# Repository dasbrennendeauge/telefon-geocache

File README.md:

# Telefon-Geocache

Ein Geocache, der in einem alten Telefon steckt. Wer den Cache findet, nimmt den
Hörer ab und wird per Sprachansage und Display durch ein kleines Rätsel geführt:
Handynummer eingeben, Münze einwerfen – das Telefon ruft daraufhin **zurück** und
verrät über die angezeigte Rufnummer einen PIN. Wird der PIN korrekt eingegeben,
öffnet ein Relais die Klappe zum Logbuch.

## Spielablauf

Die Firmware ist eine Zustandsmaschine (`step0`–`step7` in `cache/cache.ino`):

| Schritt | Anzeige / Aktion |
|---|---|
| 0 | „Hörer ans Ohr, drücke Taste 5" – GSM-Modul wird initialisiert |
| 1 | Begrüßung; Netz wird gesucht und die Uhrzeit geprüft (nur **8–22 Uhr**, sonst Schritt 7) |
| 2 | Handynummer über das Tastenfeld eingeben, Abschluss mit `#` |
| 3 | „Münze einwerfen" – Wartet auf den Münzeinwurf (Lichtschranke) |
| 4 | Server abfragen (HTTP), Absender-Rufnummer setzen lassen, dann den Spieler **anrufen** (5 s klingeln, NICHT abheben) |
| 5 | Die letzten 4 Ziffern der angezeigten Rufnummer eingeben |
| 6 | Korrekt → Relais öffnet die Klappe; falsch → Hinweis, neuer Versuch |
| 7 | Außerhalb der Öffnungszeiten → Gerät geht in den Tiefschlaf |

Ein 5-Minuten-Countdown läuft global mit; nach Ablauf legt sich das Gerät schlafen.

## So funktioniert der „Rückruf-PIN"

Der eigentliche Trick: Der Spieler muss nicht abnehmen, sondern nur die **angezeigte
Rufnummer** ablesen. Deren letzte 4 Ziffern sind der PIN.

```
Arduino (cache.ino)                        Server (index.php)            sipgate
  │  HTTP GET (über GPRS) ───────────────────▶                              
  │                                          │  PUT /devices/{id}/callerid │
  │                                          │   = +491579999<code>  ──────▶
  │  ◀──────────────── Antwort: <code> ──────┘                              
  │  GPRS trennen                                                           
  │  SIM800L wählt die Handynummer (ATD) ─────────────────────────────────▶ Telefon des
  │  5 s warten, dann auflegen (ATH)                                         Spielers klingelt
  │                                                                          mit +491579999<code>
```

Der Anruf wird seit der Umstellung auf einen **sipgate-neo-PBX-Account** direkt vom
SIM800L aufgebaut (nicht mehr über die sipgate-Click-to-Dial-API – neo erlaubt kein
Nummer-zu-Nummer-Dialing mehr). Der Server setzt nur noch die angezeigte
Absender-Rufnummer und liefert den 4-stelligen Code zurück.

## Projektstruktur

| Pfad | Inhalt |
|---|---|
| `cache/` | Arduino-Firmware (`cache.ino`) + Build-Anleitung (`BUILD.md`) |
| `lib/` | Alle Arduino-Bibliotheken, vendored (siehe unten) |
| `platformio.ini` | PlatformIO-Build-Konfiguration |
| `web-call-starter/` | PHP-Server: setzt Absender-Rufnummer & liefert PIN-Code |
| `mp3/` | Sprachansagen + Skripte zur TTS-Erzeugung (Google Cloud, Azure, AWS Polly) |
| `pcb/` | EAGLE-Schaltplan und Platinen-Layout |
| `experimente/` | Ältere Test-Sketche |

## Hardware

- **Arduino Mega 2560** (Steuerung)
- **SIM800L** GSM-Modul mit sipgate-SIM (Daten + Sprachanruf)
- **DFPlayer Mini** MP3-Modul + Lautsprecher (Sprachansagen)
- **LCD 20×4** mit I²C-Backpack
- **3×4-Tastenfeld** (Matrix)
- **Lichtschranke** als Münzeinwurf-Sensor
- **Relais** SRD-05VDC-SL-C (öffnet die Klappe)
- **Step-Up-Wandler** für die Stromversorgung des SIM800L

### Verdrahtung (Arduino Mega)

| Komponente | Pins |
|---|---|
| Tastenfeld | Zeilen 34, 35, 36, 37 · Spalten 31, 32, 33 |
| Relais | D10 |
| Münzeinwurf (analog) | A13 |
| SIM800L (UART) | `Serial1`: RX1 = D19, TX1 = D18 · 19200 Baud |
| DFPlayer Mini (UART) | `Serial3`: RX3 = D15, TX3 = D14 |
| LCD (I²C) | SDA = D20, SCL = D21 · Adresse `0x27` |

Die GSM-PIN ist in `cache/cache.ino` definiert (`GSM_PIN`).

## Firmware bauen

Der Build läuft reproduzierbar über [PlatformIO](https://platformio.org/) – alle
Details in **[`cache/BUILD.md`](cache/BUILD.md)**. Kurzform (im Repo-Wurzelverzeichnis):

```bash
pio run                 # kompilieren
pio run -t upload       # auf den Arduino Mega 2560 flashen
pio device monitor      # serieller Monitor (115200 Baud)
```

### Bibliotheken (vendored)

Alle Bibliotheken liegen mit fester Version in `lib/`, damit der Build dauerhaft
und ohne Abhängigkeit von der PlatformIO-Registry funktioniert:

| Library | Version | Anmerkung |
|---|---|---|
| TinyGSM | 0.12.0 | GSM/GPRS + Sprachanruf (SIM800) |
| ArduinoHttpClient | 0.6.1 | HTTP-Request an den Server |
| Keypad | 3.1.1 | Tastenfeld |
| DFMiniMp3 | 1.0.5 | bewusst alte Version – ab 1.0.6 inkompatible Callback-API |
| LiquidCrystal_I2C | fdebrabander | LCD-Ansteuerung über I²C |

## Server (`web-call-starter`)

Kleiner PHP-Endpunkt, der bei jedem Aufruf eine zufällige 4-stellige Zahl erzeugt,
diese als Absender-Rufnummer am sipgate-Gerät setzt und den Code als Antwort
zurückgibt.

- **`SIPGATE_CREDENTIALS`** muss als Umgebungsvariable gesetzt sein
  (Base64 von `tokenId:token` des sipgate-Accounts).
- `$deviceId` in `index.php` an das eigene sipgate-Gerät anpassen (neo nutzt oft `e0`/`p0`).
- Keine externen Abhängigkeiten: reines PHP mit cURL, kein Composer nötig.
- `telefoncache.vhost` enthält eine Beispiel-Apache-vHost-Konfiguration.

> Hinweis: Der eigentliche Anruf erfolgt nicht mehr serverseitig, sondern direkt
> vom Arduino (siehe oben).

## Sprachansagen (`mp3`)

Die Ansagen `0001.mp3`–`0008.mp3` entsprechen den Spielschritten und werden vom
DFPlayer Mini abgespielt. Sie lassen sich per Text-to-Speech neu erzeugen; im
Ordner `mp3/` liegen Skripte für **Google Cloud TTS**, **Azure** und **AWS Polly**.
Die zugehörigen Texte stehen in `mp3/texte/`.

## Platine (`pcb`)

EAGLE-Dateien (`*.sch` Schaltplan, `*.brd` Layout) inklusive gerenderter
Vorschaubilder und PDF-Export.

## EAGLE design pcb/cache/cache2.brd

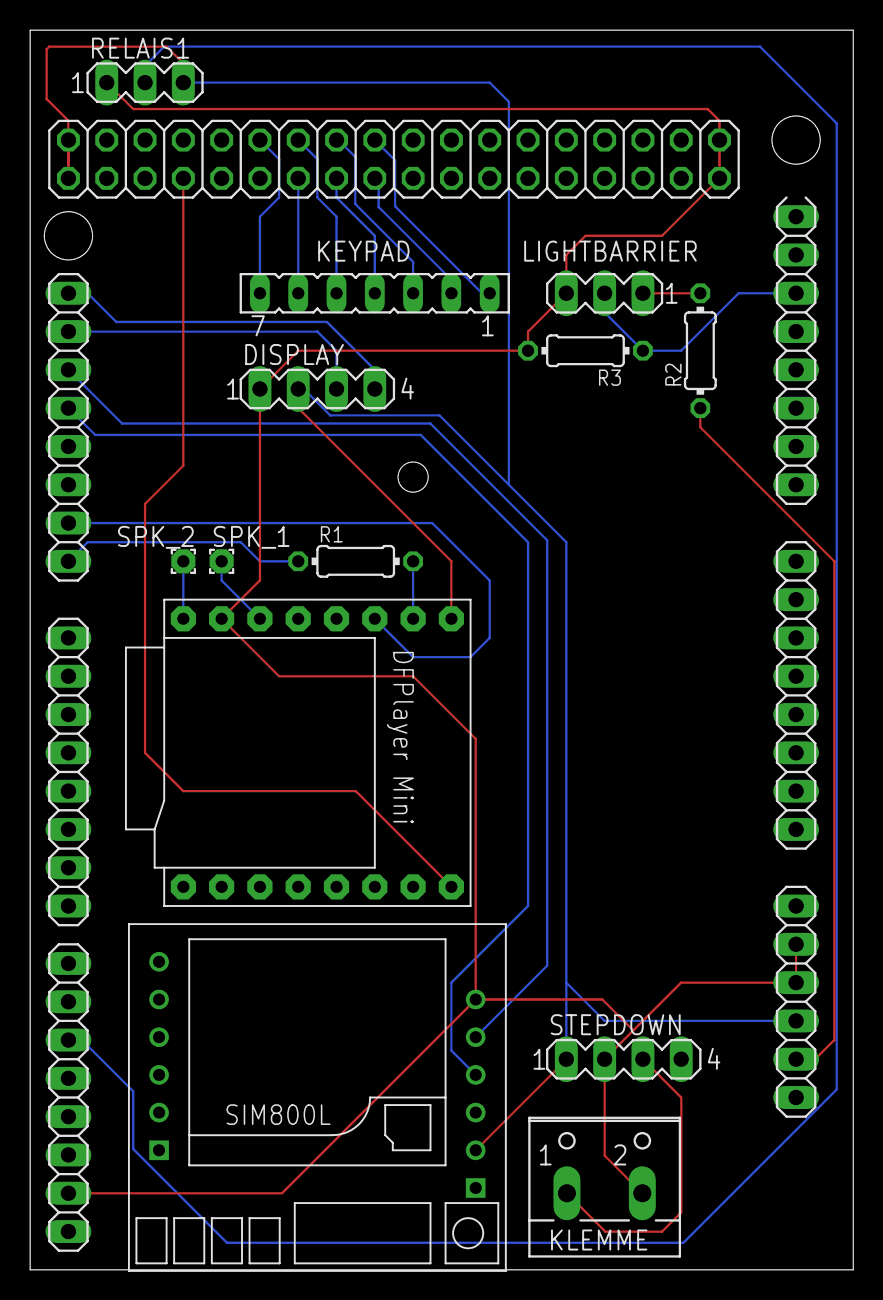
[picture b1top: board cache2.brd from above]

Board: 2 copper layers, 54.6 x 82.2 mm, 14 parts (0 on the bottom side), 24 nets.

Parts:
DISPLAY: MA04-1
IC1: MEGA_ARDUINO
KEYPAD: FE07
KLEMME: W237-102
LIGHTBARRIER: MA03-1
R1, R2, R3: 0204/7
RELAIS1: MA03-1
SPK_1, SPK_2: 1,6/0,8
STEPDOWN: MA04-1
U$1: DFPLAYER
U$2: SIM800LMODULE

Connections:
3V3: LIGHTBARRIER.1, R2.2
+5V: DISPLAY.2, IC1.3, IC1.47, IC1.48, RELAIS1.3, STEPDOWN.1, U$1.VCC, U$2.VCC
GND: DISPLAY.1, IC1.4, IC1.5, IC1.45, IC1.81, IC1.82, KLEMME.2, LIGHTBARRIER.3, R3.2, RELAIS1.1, STEPDOWN.2, U$1.GND_1, U$2.GND
IN+: KLEMME.1, STEPDOWN.3
IN-B: IC1.20, LIGHTBARRIER.2, R3.1
unnamed: IC1.25, U$2.TX
unnamed: IC1.26, U$2.RX
unnamed: IC1.41, RELAIS1.2
unnamed: DISPLAY.3, IC1.24
unnamed: DISPLAY.4, IC1.23
unnamed: IC1.58, KEYPAD.7
unnamed: IC1.59, KEYPAD.6
unnamed: IC1.60, KEYPAD.5
unnamed: IC1.61, KEYPAD.4
unnamed: IC1.62, KEYPAD.3
unnamed: IC1.63, KEYPAD.2
unnamed: IC1.64, KEYPAD.1
unnamed: IC1.30, R1.1
unnamed: IC1.29, U$1.TX
unnamed: R1.2, U$1.RX
unnamed: IC1.2, R2.1
unnamed: SPK_2.1, U$1.SPK2
unnamed: SPK_1.1, U$1.SPK1
unnamed: IC1.53, U$1.BUSY

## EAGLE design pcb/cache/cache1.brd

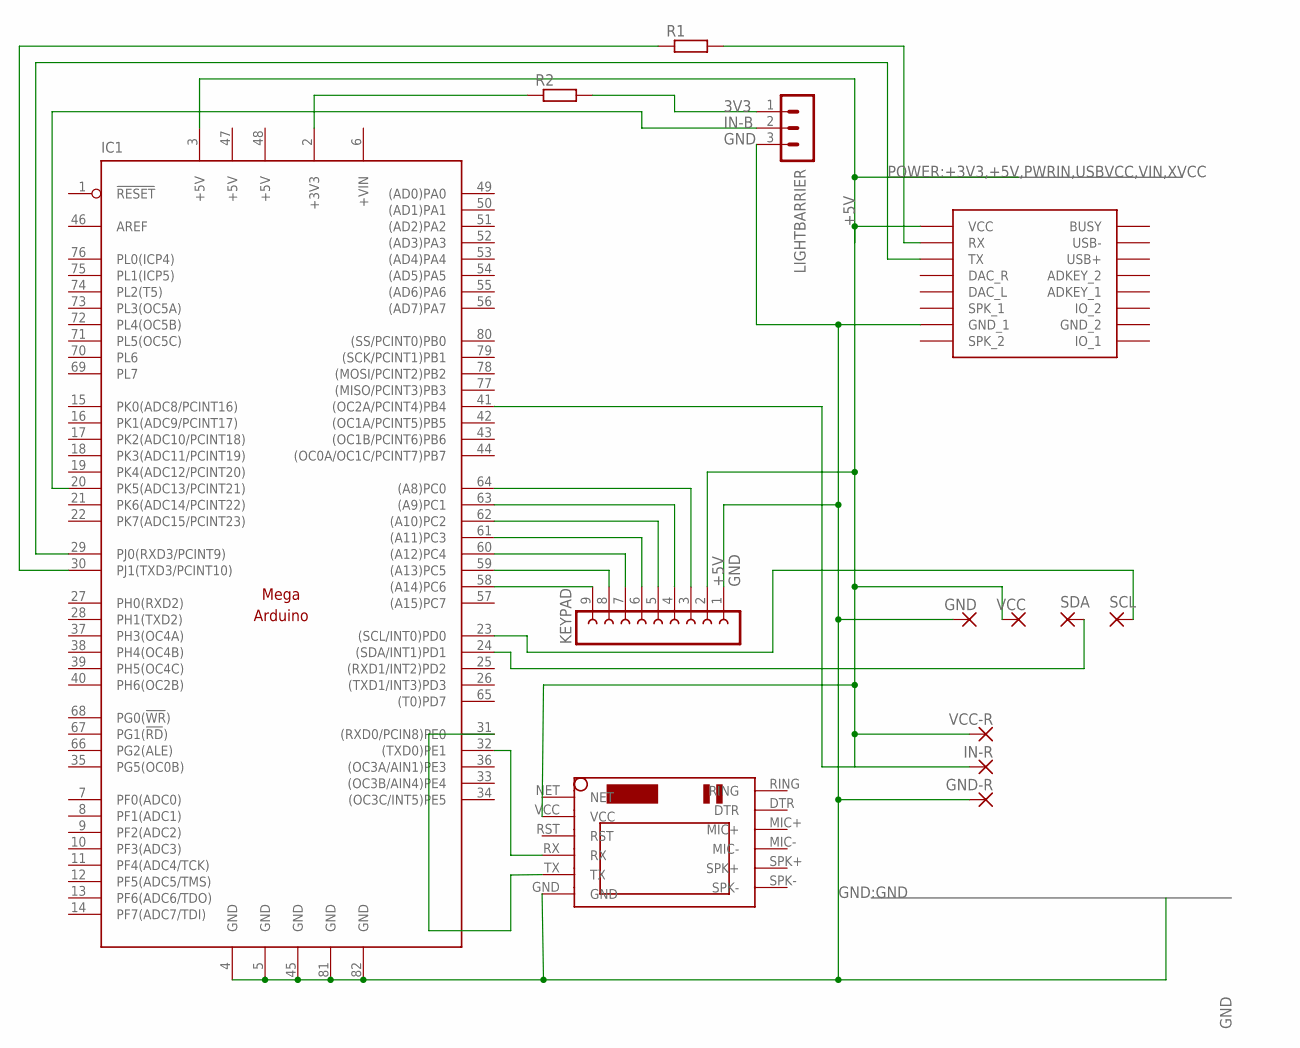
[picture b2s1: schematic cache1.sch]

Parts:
GND: 1,6/0,8
GND-R: 1,6/0,8
IC1: MEGAARDUINO_1; MEGA_ARDUINO
IN-R: 1,6/0,8
KEYPAD: FE09-1; FE09
LIGHTBARRIER: MA03-1
R1, R2: R-EU_0204/7; 0204/7
SCL: 1,6/0,8
SDA: 1,6/0,8
U$1: DFPLAYER
U$2: SIM800LMODULE
VCC: 1,6/0,8
VCC-R: 1,6/0,8

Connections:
3V3: LIGHTBARRIER.1, R2.2
+5V: IC1.3 (+5V), IC1.47 (+5V), IC1.48 (+5V), KEYPAD.2, U$1.VCC, U$2.VCC, VCC.1, VCC-R.1
+VIN: IC1.6 (+VIN)
GND: GND.1, GND-R.1, IC1.4 (GND), IC1.5 (GND), IC1.45 (GND), IC1.81 (GND), IC1.82 (GND), KEYPAD.1, LIGHTBARRIER.3, U$1.GND_1, U$2.GND
IN-B: IC1.20 (PK5(ADC13/PCINT21)), LIGHTBARRIER.2
unnamed: IC1.31 ((RXD0/PCIN8)PE0), U$2.TX
unnamed: IC1.32 ((TXD0)PE1), U$2.RX
unnamed: IC1.41 ((OC2A/PCINT4)PB4), IN-R.1
unnamed: IC1.24 ((SDA/INT1)PD1), SDA.1
unnamed: IC1.23 ((SCL/INT0)PD0), SCL.1
unnamed: IC1.58 ((A14)PC6), KEYPAD.9
unnamed: IC1.59 ((A13)PC5), KEYPAD.8
unnamed: IC1.60 ((A12)PC4), KEYPAD.7
unnamed: IC1.61 ((A11)PC3), KEYPAD.6
unnamed: IC1.62 ((A10)PC2), KEYPAD.5
unnamed: IC1.63 ((A9)PC1), KEYPAD.4
unnamed: IC1.64 ((A8)PC0), KEYPAD.3
unnamed: IC1.30 (PJ1(TXD3/PCINT10)), R1.1
unnamed: IC1.29 (PJ0(RXD3/PCINT9)), U$1.TX
unnamed: R1.2, U$1.RX
unnamed: IC1.2 (+3V3), R2.1

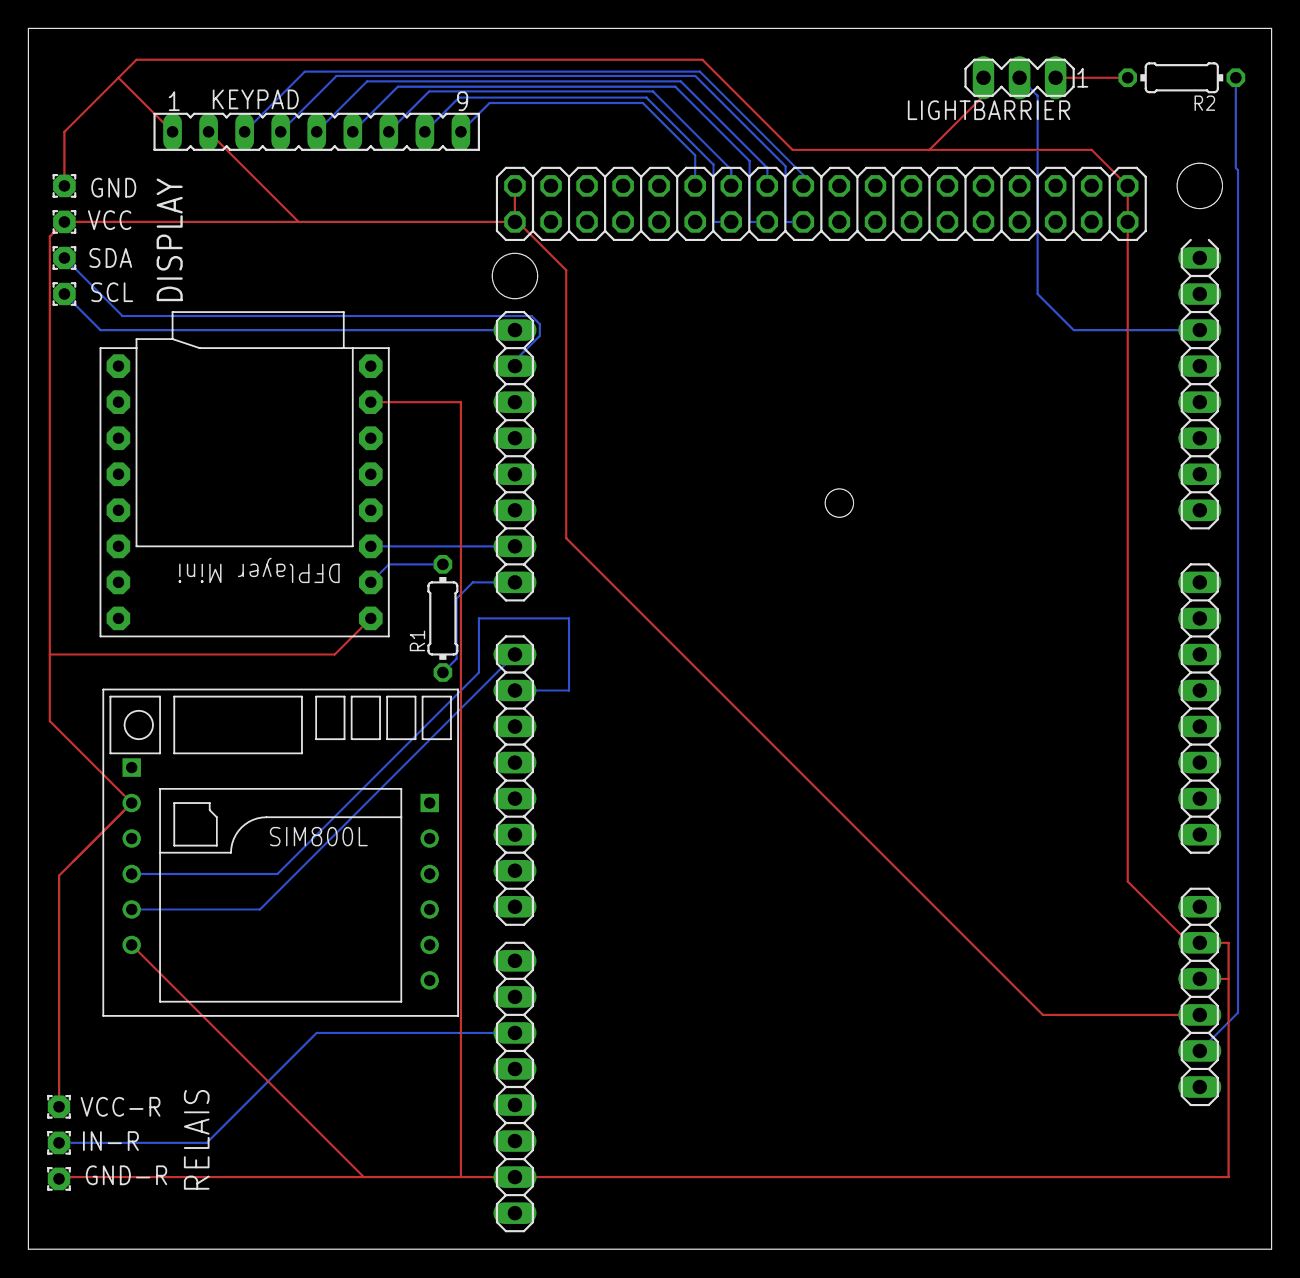
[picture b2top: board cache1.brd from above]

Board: 2 copper layers, 87.6 x 86.0 mm, 14 parts (0 on the bottom side), 20 nets.

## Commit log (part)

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2019-03-05 erster commit
2019-03-05 zeilen gelöscht
2019-03-05 mp3 hinzugefuegt
2019-03-05 schritt 1: display anzeige und counter
2019-03-06 Formatierung und Wort "Sekunden" beim Countdown hinzugefügt
2019-03-12 weiter bis GSM
2019-04-03 spielereien mit dem GSM modul
2019-04-30 Muenzeinwurf funktioniert, PIN-Eingabe, Ergebnisanzeige
2019-07-18 funktionierender Anruf mit nano
2019-07-31 added php script to start and hang up call - returns PIN code
2019-08-08 funktionierende Beispiele mit Nano und GSM
2019-08-08 abschnitt für mega hinzugefügt
2019-08-08 cache zum ersten mal mit GSM
2019-08-16 mp3 abspielen hinzugefügt
2019-08-22 anruf mit nummerneingabe
2019-08-22 relais hinzugefuegt
2019-09-03 formatierer fuer nummern hinzugefuegt
2019-09-03 countryCode korrigiert
2019-10-02 PCB hinzugefuegt
2019-11-15 updated pcb
2019-11-28 created text files and scripts for polly, azure and gcloud
2020-01-07 funktionierender code
2020-01-07 umlaute nun richtig
2026-06-17 letzten codestand wieder gefunden
2026-06-25 Schleifen und hobeln
